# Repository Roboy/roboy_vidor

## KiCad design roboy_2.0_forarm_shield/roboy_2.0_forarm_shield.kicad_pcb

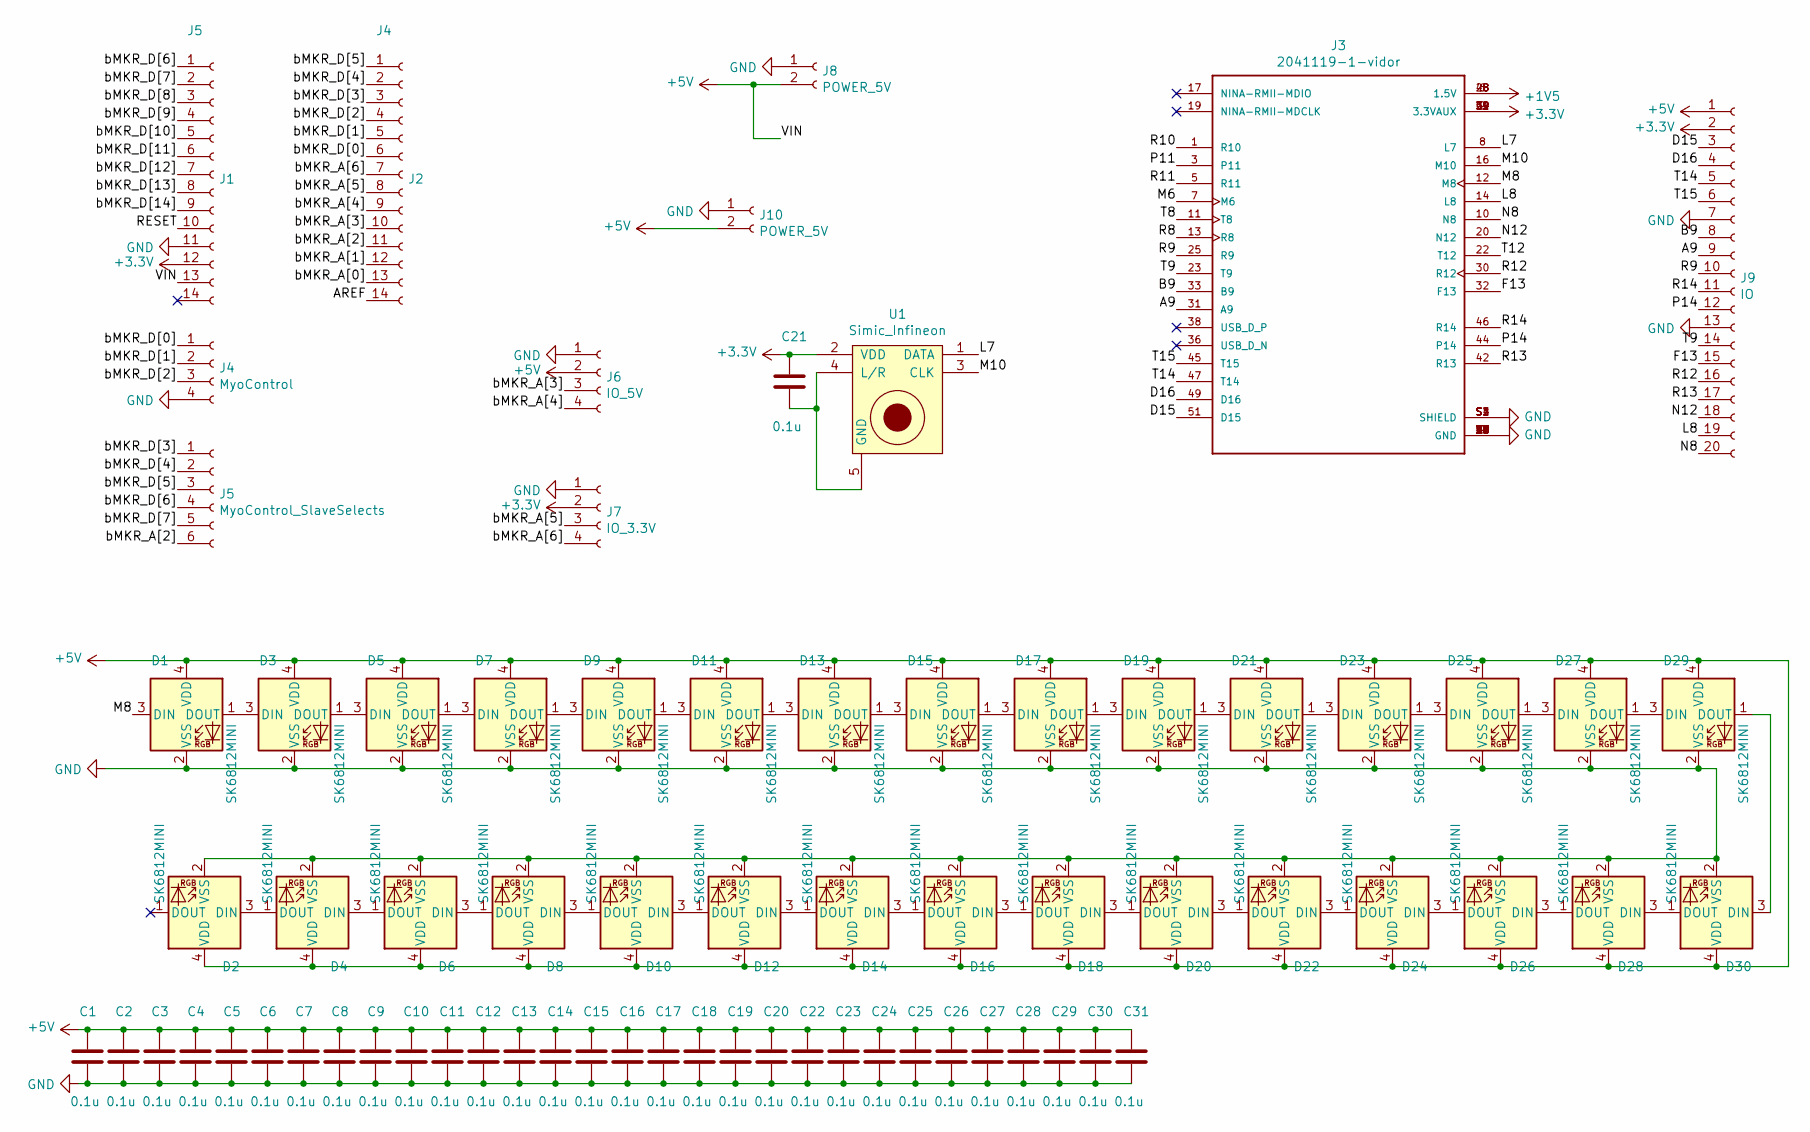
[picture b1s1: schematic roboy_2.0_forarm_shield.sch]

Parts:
C1, C2, C3, C4, C5, C6, C7, C8, C9, C10, C11, C12, C13, C14, C15, C16, C17, C18, C19, C20, C21, C22, C23, C24, C25, C26, C27, C28, C29, C30, C31: 0.1u; R_0402_1005Metric
D1, D2, D3, D4, D5, D6, D7, D8, D9, D10, D11, D12, D13, D14, D15, D16, D17, D18, D19, D20, D21, D22, D23, D24, D25, D26, D27, D28, D29, D30: SK6812MINI; LED_SK6812MINI_PLCC4_3.5x3.5mm_P1.75mm
J1: J5; PinHeader_1x14_P2.54mm_Vertical
J2: J4; PinHeader_1x14_P2.54mm_Vertical
J3: 2041119-1-vidor; TE_2041119-1
J4: MyoControl; TE-Connectivity_Micro-Match_connector_02x02_Pitch_1.27mm
J5: MyoControl_SlaveSelects; TE-Connectivity_Micro-Match_connector_02x03_Pitch_1.27mm
J6: IO_5V; TE-Connectivity_Micro-Match_connector_02x02_Pitch_1.27mm
J7: IO_3.3V; TE-Connectivity_Micro-Match_connector_02x02_Pitch_1.27mm
J8, J10: POWER_5V; Wago_2060_2_SMD
J9: IO; TE-Connectivity_Micro-Match_connector_02x10_Pitch_1.27mm
U1: Simic_Infineon; IM69D130_Simic_uPhone

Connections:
+1V5: J3.6 (1.5V), J3.28 (1.5V), J3.48 (1.5V)
+3V3: C21.1, J1.12, J3.2 (3.3VAUX), J3.24 (3.3VAUX), J3.39 (3.3VAUX), J3.41 (3.3VAUX), J3.52 (3.3VAUX), J7.2, J9.2, U1.2 (VDD)
+5V: C1.1, C2.1, C3.1, C4.1, C5.1, C6.1, C7.1, C8.1, C9.1, C10.1, C11.1, C12.1, C13.1, C14.1, C15.1, C16.1, C17.1, C18.1, C19.1, C20.1, C22.1, C23.1, C24.1, C25.1, C26.1, C27.1, C28.1, C29.1, C30.1, C31.1, D1.4 (VDD), D2.4 (VDD), D3.4 (VDD), D4.4 (VDD), D5.4 (VDD), D6.4 (VDD), D7.4 (VDD), D8.4 (VDD), D9.4 (VDD), D10.4 (VDD), D11.4 (VDD), D12.4 (VDD), D13.4 (VDD), D14.4 (VDD), D15.4 (VDD), D16.4 (VDD), D17.4 (VDD), D18.4 (VDD), D19.4 (VDD), D20.4 (VDD), D21.4 (VDD), D22.4 (VDD), D23.4 (VDD), D24.4 (VDD), D25.4 (VDD), D26.4 (VDD), D27.4 (VDD), D28.4 (VDD), D29.4 (VDD), D30.4 (VDD), J1.13, J6.2, J8.2, J9.1, J10.2
/A9: J3.31 (A9), J9.9
/AREF: J2.14
/B9: J3.33 (B9), J9.8
/D15: J3.51 (D15), J9.3
/D16: J3.49 (D16), J9.4
/F13: J3.32 (F13), J9.15
/L7: J3.8 (L7), U1.1 (DATA)
/L8: J3.14 (L8), J9.19
/M6: J3.7 (M6)
/M8: D1.3 (DIN), J3.12 (M8)
/M10: J3.16 (M10), U1.3 (CLK)
/N8: J3.10 (N8), J9.20
/N12: J3.20 (N12), J9.18
/P11: J3.3 (P11)
/P14: J3.44 (P14), J9.12
/R8: J3.13 (R8)
/R9: J3.25 (R9), J9.10
/R10: J3.1 (R10)
/R11: J3.5 (R11)
/R12: J3.30 (R12), J9.16
/R13: J3.42 (R13), J9.17
/R14: J3.46 (R14), J9.11
/RESET: J1.10
/T8: J3.11 (T8)
/T9: J3.23 (T9), J9.14
/T12: J3.22 (T12)
/T14: J3.47 (T14), J9.5
/T15: J3.45 (T15), J9.6
/bMKR_A[0]: J2.13
/bMKR_A[1]: J2.12
/bMKR_A[2]: J2.11, J5.6
/bMKR_A[3]: J2.10, J6.3
/bMKR_A[4]: J2.9, J6.4
/bMKR_A[5]: J2.8, J7.3
/bMKR_A[6]: J2.7, J7.4
/bMKR_D[0]: J2.6, J4.1
/bMKR_D[1]: J2.5, J4.2
/bMKR_D[2]: J2.4, J4.3
/bMKR_D[3]: J2.3, J5.1
/bMKR_D[4]: J2.2, J5.2
/bMKR_D[5]: J2.1, J5.3
/bMKR_D[6]: J1.1, J5.4
/bMKR_D[7]: J1.2, J5.5
/bMKR_D[8]: J1.3
/bMKR_D[9]: J1.4
/bMKR_D[10]: J1.5
/bMKR_D[11]: J1.6
/bMKR_D[12]: J1.7
/bMKR_D[13]: J1.8
/bMKR_D[14]: J1.9
GND: C1.2, C2.2, C3.2, C4.2, C5.2, C6.2, C7.2, C8.2, C9.2, C10.2, C11.2, C12.2, C13.2, C14.2, C15.2, C16.2, C17.2, C18.2, C19.2, C20.2, C22.2, C23.2, C24.2, C25.2, C26.2, C27.2, C28.2, C29.2, C30.2, C31.2, D1.2 (VSS), D2.2 (VSS), D3.2 (VSS), D4.2 (VSS), D5.2 (VSS), D6.2 (VSS), D7.2 (VSS), D8.2 (VSS), D9.2 (VSS), D10.2 (VSS), D11.2 (VSS), D12.2 (VSS), D13.2 (VSS), D14.2 (VSS), D15.2 (VSS), D16.2 (VSS), D17.2 (VSS), D18.2 (VSS), D19.2 (VSS), D20.2 (VSS), D21.2 (VSS), D22.2 (VSS), D23.2 (VSS), D24.2 (VSS), D25.2 (VSS), D26.2 (VSS), D27.2 (VSS), D28.2 (VSS), D29.2 (VSS), D30.2 (VSS), J1.11, J3.4 (GND), J3.9 (GND), J3.15 (GND), J3.18 (GND), J3.21 (GND), J3.26 (GND), J3.27 (GND), J3.29 (GND), J3.34 (GND), J3.35 (GND), J3.37 (GND), J3.40 (GND), J3.43 (GND), J3.50 (GND), J3.S1 (SHIELD), J3.S2 (SHIELD), J3.S3 (SHIELD), J3.S4 (SHIELD), J4.4, J6.1, J7.1, J8.1, J9.7, J9.13, J10.1
unnamed: C21.2, U1.4 (L/R), U1.5 (GND)
unnamed: D1.1 (DOUT), D3.3 (DIN)
unnamed: D2.3 (DIN), D4.1 (DOUT)
unnamed: D3.1 (DOUT), D5.3 (DIN)
unnamed: D4.3 (DIN), D6.1 (DOUT)
unnamed: D5.1 (DOUT), D7.3 (DIN)
unnamed: D6.3 (DIN), D8.1 (DOUT)
unnamed: D7.1 (DOUT), D9.3 (DIN)
unnamed: D8.3 (DIN), D10.1 (DOUT)
unnamed: D10.3 (DIN), D12.1 (DOUT)
unnamed: D11.1 (DOUT), D13.3 (DIN)
unnamed: D9.1 (DOUT), D11.3 (DIN)
unnamed: D12.3 (DIN), D14.1 (DOUT)
unnamed: D13.1 (DOUT), D15.3 (DIN)
unnamed: D14.3 (DIN), D16.1 (DOUT)
unnamed: D15.1 (DOUT), D17.3 (DIN)
unnamed: D16.3 (DIN), D18.1 (DOUT)
unnamed: D17.1 (DOUT), D19.3 (DIN)
unnamed: D18.3 (DIN), D20.1 (DOUT)
unnamed: D19.1 (DOUT), D21.3 (DIN)
unnamed: D20.3 (DIN), D22.1 (DOUT)
unnamed: D21.1 (DOUT), D23.3 (DIN)
unnamed: D22.3 (DIN), D24.1 (DOUT)
unnamed: D23.1 (DOUT), D25.3 (DIN)
unnamed: D24.3 (DIN), D26.1 (DOUT)
unnamed: D25.1 (DOUT), D27.3 (DIN)
unnamed: D26.3 (DIN), D28.1 (DOUT)
unnamed: D27.1 (DOUT), D29.3 (DIN)
unnamed: D28.3 (DIN), D30.1 (DOUT)
unnamed: D29.1 (DOUT), D30.3 (DIN)

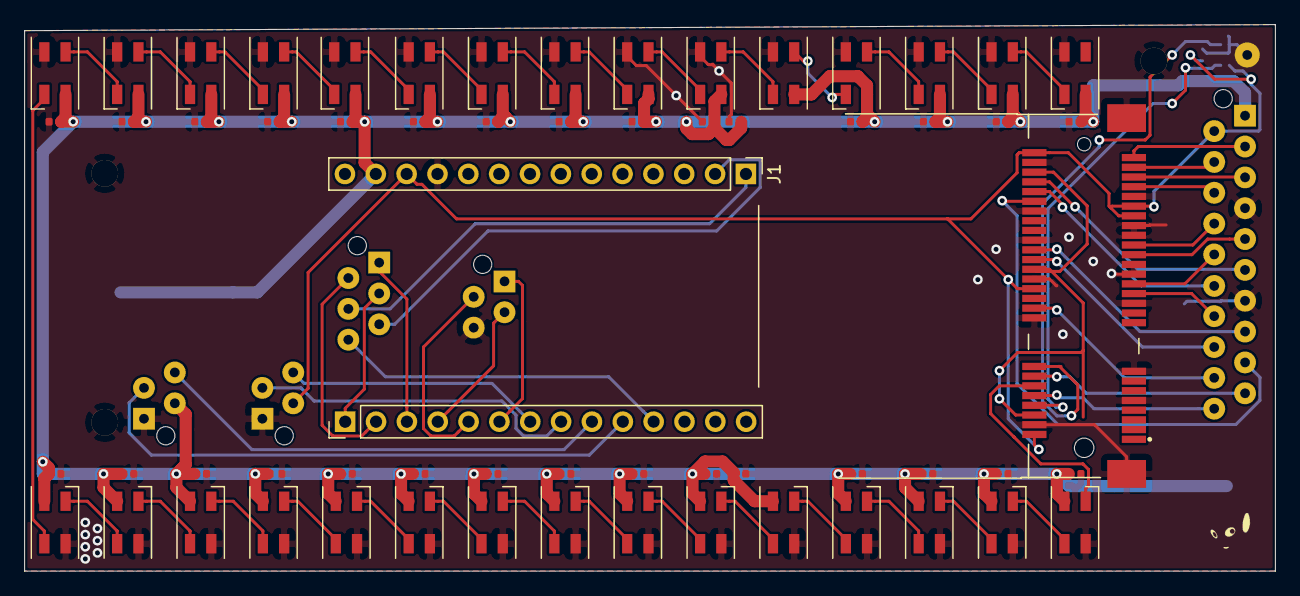
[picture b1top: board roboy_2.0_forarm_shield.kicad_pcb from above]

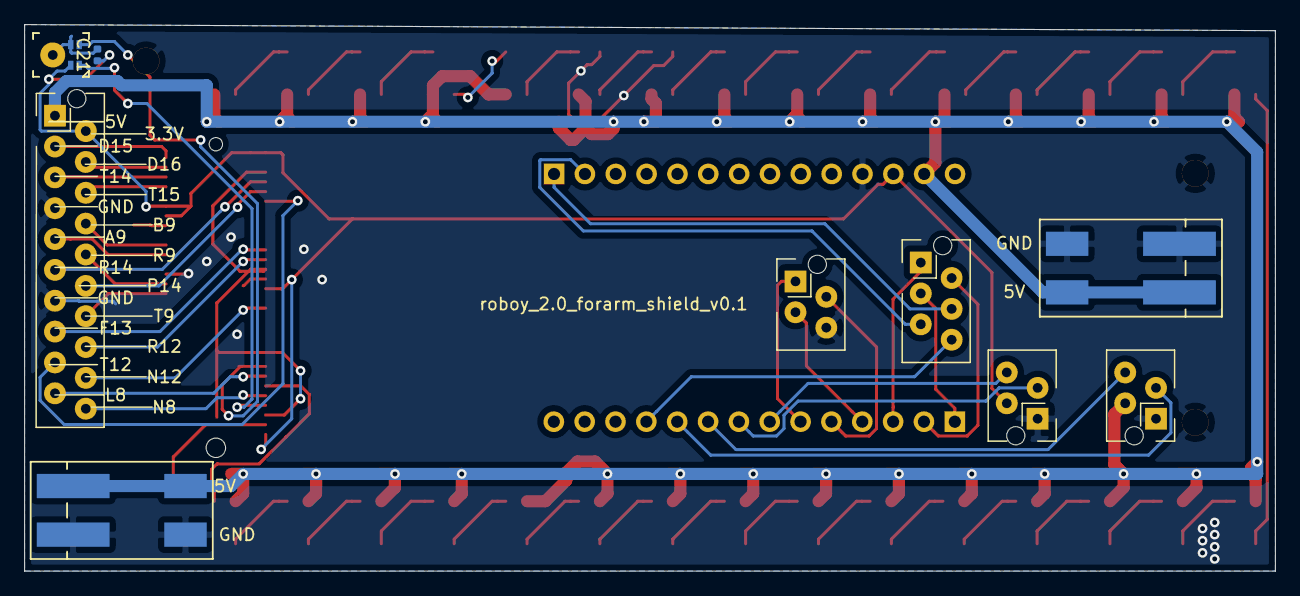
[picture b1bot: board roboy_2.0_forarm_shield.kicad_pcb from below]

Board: 2 copper layers, 103.0 x 45.0 mm, 72 parts (9 on the bottom side), 66 nets.

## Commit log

2019-02-07 initial vidor project
2019-02-07 with myocontrol draft
2019-02-09 vidor flash via arduno works
2019-02-10 spi communication between samd and fpga working
2019-02-10 with connection to myoControl
2019-02-10 works with myoMuscle :)
2019-02-10 with command frames via udp
2019-02-12 with resetFPGA script
2019-02-12 works
2019-02-13 controlling 6 bldc motors
2019-02-14 more values
2019-02-15 with udp draft
2019-02-15 bababaaaam
2019-03-20 with ts4231
2019-03-25 experiments
2019-08-10 with status printouts on serial port
2019-08-10 vidor forearm shield ordered on aisler
2019-08-11 simplifiying
2019-08-11 workaround because unions are not supported, mofos
2019-08-12 floating point units too big for vidor, moving to fixed point
2019-08-12 works with pwm
2019-08-12 with quadrature decoder
2019-08-13 trying different filter parameters
2019-08-15 cw ccw
2019-08-16 with pd control
2019-08-19 with draft for current sensor readout via spi
2019-08-22 minor changes
2019-08-22 with forearm control
2019-09-13 sleep less
2019-09-15 not verifying the flash takes a lot less time
2019-10-18 better
